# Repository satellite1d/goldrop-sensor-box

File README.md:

# goldrop-sensor-box
Temperature and humidity sensor through wifi with 230VAC power input.

The device runs on ESP32-C3-WROOM chip utilizing the built in wifi antenna, and can be powered with usb-c or up to 230V mains.
Main purpose of the device is to collect temperature and humidity data and sending it to a server through wifi in real time.
Firmware has been vibe coded.

## Firmware
Current firmware 0.6.1 for ESP32-C3 using ESP-IDF 6.1 and PlatformIO.
more info in [`goldrop-fw/`](goldrop-fw/) 

## Schematic

Pliki schematu, PCB i bibliotek: [KiCad/](KiCad/).

## PCB design
TODO: 
  - add a picture with all components
  - varistor might not be necessary
  - maybe change the LDO to a bigger one for better longevity 

## Case design
TODO: add case photo and files

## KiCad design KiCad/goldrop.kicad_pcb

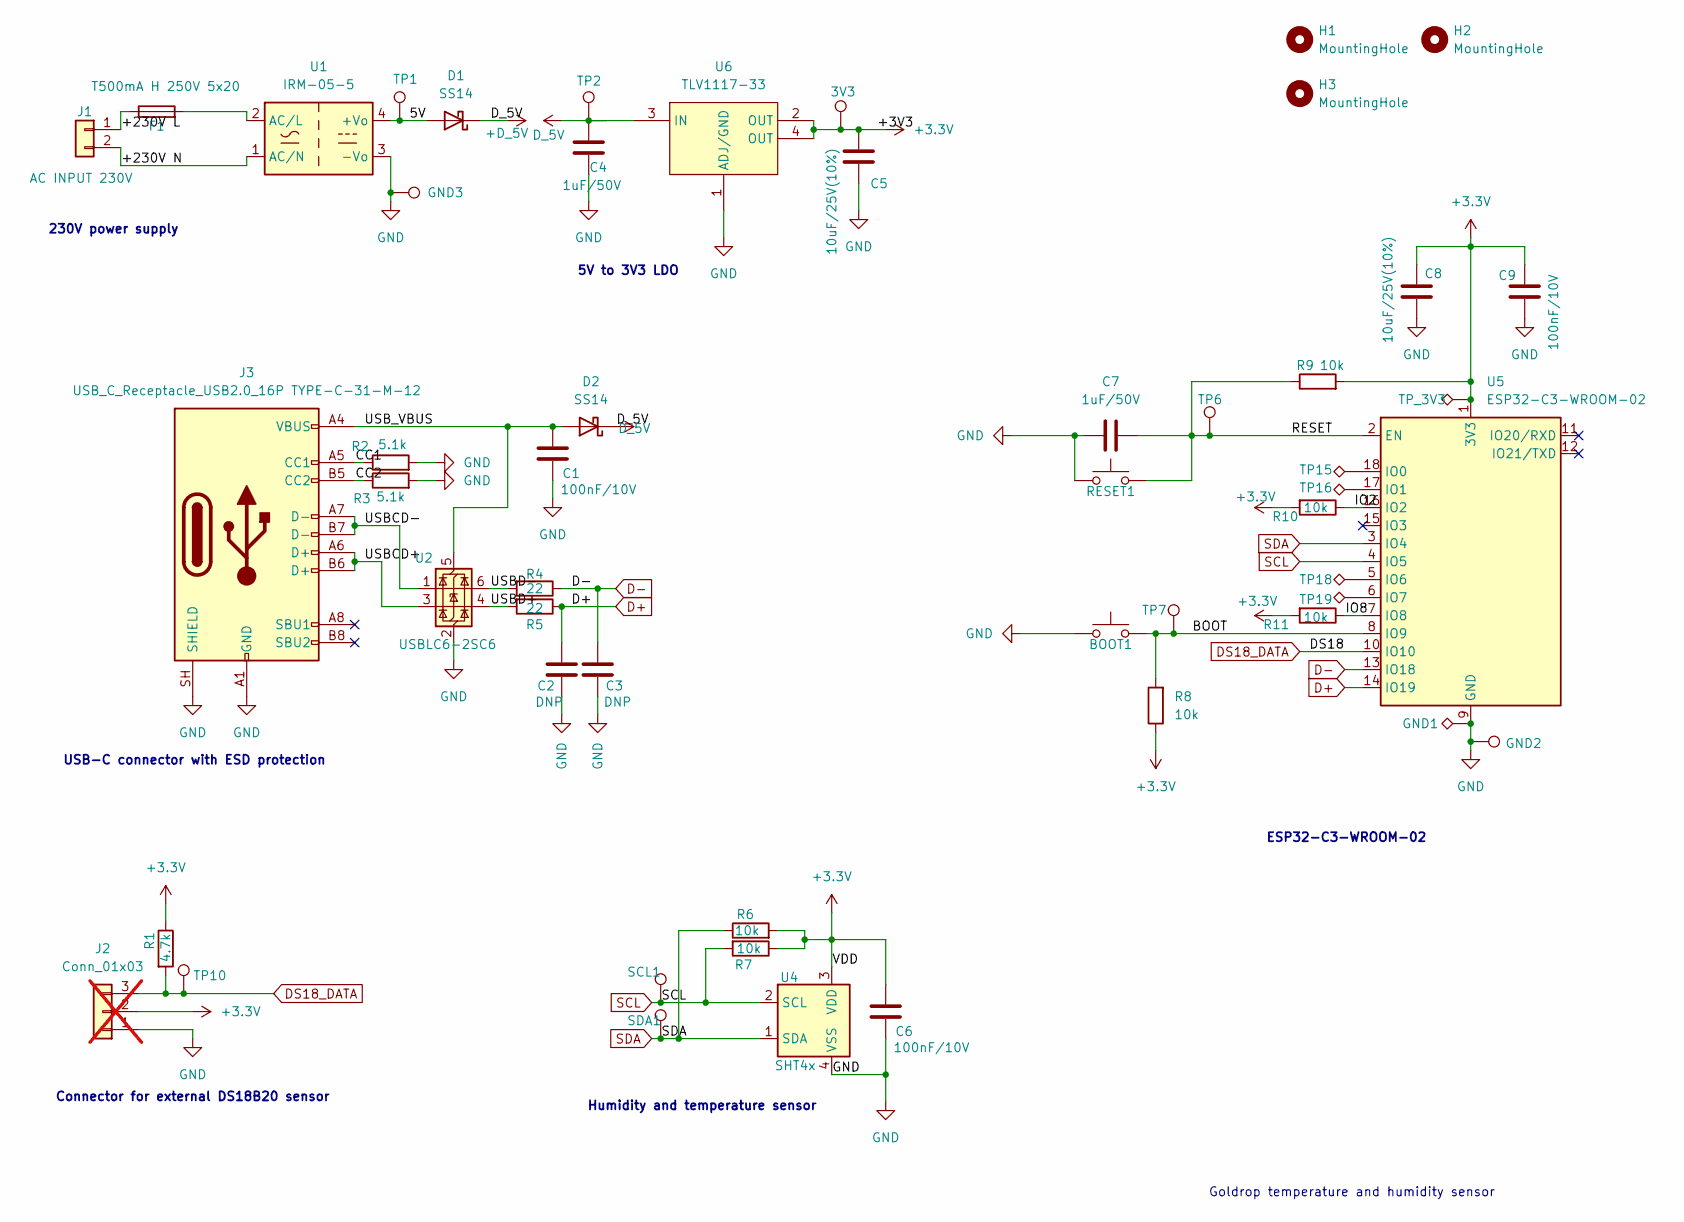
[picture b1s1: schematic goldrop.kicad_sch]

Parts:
3V3: TestPoint; TestPoint_Pad_D1.5mm
BOOT1: SW_Push; SW-SMD_L3.9-W3.0-P4.45; MPN TS-1088-AR02016; LCSC C720477
C1, C6, C9: 100nF/10V; C_0805_2012Metric_Pad1.18x1.45mm_HandSolder; MPN CC0805KRX7R9BB104; LCSC C49678
C2, C3: DNP; C_0805_2012Metric_Pad1.18x1.45mm_HandSolder
C4, C7: 1uF/50V; C_0805_2012Metric_Pad1.18x1.45mm_HandSolder; MPN CL21B105KBFNNNE; LCSC C28323
C5, C8: 10uF/25V(10%); C_0805_2012Metric_Pad1.18x1.45mm_HandSolder; MPN CL21A106KAYNNNE; LCSC C15850
D1, D2: SS14; D_SMA; MPN SS14; LCSC C2480
F1: T500mA H 250V 5x20; FUSE-TH_L22.6-W9.0; MPN 5x20 BLX-A XC-7; LCSC C3131
GND1: TestPoint_Alt; TestPoint_Pad_1.0x1.0mm
GND2, GND3: TestPoint; TestPoint_Pad_D1.5mm
H1, H2, H3: MountingHole; MountingHole_3.2mm_M3
J1: AC INPUT 230V; CONN-TH_2P-P7.62_DB910-7.62-2P; MPN DB910-7.62-2P-GN-S; LCSC C395876
J2: Conn_01x03; CONN-TH_3P-P5.08_KF129-5.08-3P; MPN KF129-5.08-3P; LCSC C475093; not fitted
J3: USB_C_Receptacle_USB2.0_16P TYPE-C-31-M-12; USB_C_Receptacle_HRO_TYPE-C-31-M-12; MPN TYPE-C-31-M-12; LCSC C165948
R1: 4.7k; R_0805_2012Metric_Pad1.20x1.40mm_HandSolder; MPN 0805W8F4701T5E; LCSC C17673
R2, R3: 5.1k; R_0805_2012Metric_Pad1.20x1.40mm_HandSolder; MPN 0805W8F5101T5E; LCSC C27834
R4, R5: 22; R_0805_2012Metric_Pad1.20x1.40mm_HandSolder; MPN 0805W8F220JT5E; LCSC C17561
R6, R7, R8, R9, R10, R11: 10k; R_0805_2012Metric_Pad1.20x1.40mm_HandSolder; MPN 0805W8F1002T5E; LCSC C17414
RESET1: SW_Push; SW-SMD_L3.9-W3.0-P4.45; MPN TS-1088-AR02016; LCSC C720477
SCL1: TestPoint; TestPoint_Pad_D1.5mm
SDA1: TestPoint; TestPoint_Pad_D1.5mm
TP1, TP2, TP6, TP7, TP10: TestPoint; TestPoint_Pad_D1.5mm
TP15, TP16, TP18, TP19: TestPoint_Alt; TestPoint_Pad_1.0x1.0mm
TP_3V3: TestPoint_Alt; TestPoint_Pad_1.0x1.0mm
U1: IRM-05-5; Converter_ACDC_MeanWell_IRM-05-xx_THT; MPN IRM-05-5; LCSC C48603696
U2: USBLC6-2SC6; SOT-23-6; MPN USBLC6-2SC6; LCSC C7519
U4: SHT4x; Sensirion_DFN-4_1.5x1.5mm_P0.8mm_SHT4x_NoCentralPad; MPN SHT45-AD1F-R2; LCSC C5360602
U5: ESP32-C3-WROOM-02; MPN ESP32-C3-WROOM-02-N4; LCSC C2934560
U6: TLV1117-33; SOT-223_L6.7-W3.5-P2.30-BR; MPN TLV1117LV33DCYR; LCSC C15578

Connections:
+3.3V: 3V3.1 (1_1), C5.2, C6.2, C8.2, C9.2, J2.2, R1.1, R6.2, R7.1, R8.1, R9.2, R10.2, R11.2, TP_3V3.1 (1_1), U4.3 (VDD), U5.1 (3V3), U6.2 (OUT), U6.4 (OUT)
+D_5V: C4.2, D1.1 (K), D2.1 (K), TP2.1 (1_1), U6.3 (IN)
/5V: D1.2 (A), TP1.1 (1_1), U1.4 (+Vo)
/+230V L: F1.1, J1.1
/+230V N: J1.2, U1.1 (AC/N)
/BOOT: BOOT1.2, R8.2, TP7.1 (1_1), U5.8 (IO9)
/CC1: J3.A5 (CC1), R2.1
/CC2: J3.B5 (CC2), R3.1
/IO2: R10.1, U5.16 (IO2)
/IO8: R11.1, U5.7 (IO8)
/RESET: C7.2, R9.1, RESET1.2, TP6.1 (1_1), U5.2 (EN)
/USBCD+: J3.A6 (D+), J3.B6 (D+), U2.3 (I/O2)
/USBCD-: J3.A7 (D-), J3.B7 (D-), U2.1 (I/O1)
/USBD+: R5.2, U2.4 (I/O2)
/USBD-: R4.2, U2.6 (I/O1)
/USB_VBUS: C1.2, D2.2 (A), J3.A4 (VBUS), J3.A9 (VBUS), J3.B4 (VBUS), J3.B9 (VBUS), U2.5 (VBUS)
D+: C2.2, R5.1, U5.14 (IO19)
D-: C3.2, R4.1, U5.13 (IO18)
DS18_DATA: J2.3, R1.2, TP10.1 (1_1), U5.10 (IO10)
GND: BOOT1.1, C1.1, C2.1, C3.1, C4.1, C5.1, C6.1, C7.1, C8.1, C9.1, GND1.1 (1_1), GND2.1 (1_1), GND3.1 (1_1), J2.1, J3.A1 (GND), J3.A12 (GND), J3.B1 (GND), J3.B12 (GND), J3.SH (SHIELD), R2.2, R3.2, RESET1.1, U1.3 (-Vo), U2.2 (GND), U4.4 (VSS), U5.9 (GND), U5.19 (GND), U6.1 (ADJ/GND)
unnamed: F1.2, U1.2 (AC/L)
unnamed: TP15.1 (1_1), U5.18 (IO0)
unnamed: TP16.1 (1_1), U5.17 (IO1)
unnamed: TP18.1 (1_1), U5.5 (IO6)
unnamed: TP19.1 (1_1), U5.6 (IO7)
SCL: R7.2, SCL1.1 (1_1), U4.2 (SCL), U5.4 (IO5)
SDA: R6.1, SDA1.1 (1_1), U4.1 (SDA), U5.3 (IO4)

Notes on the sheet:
Connector for external DS18B20 sensor
Humidity and temperature sensor
USB-C connector with ESD protection
230V power supply
Goldrop temperature and humidity sensor
ESP32-C3-WROOM-02
5V to 3V3 LDO

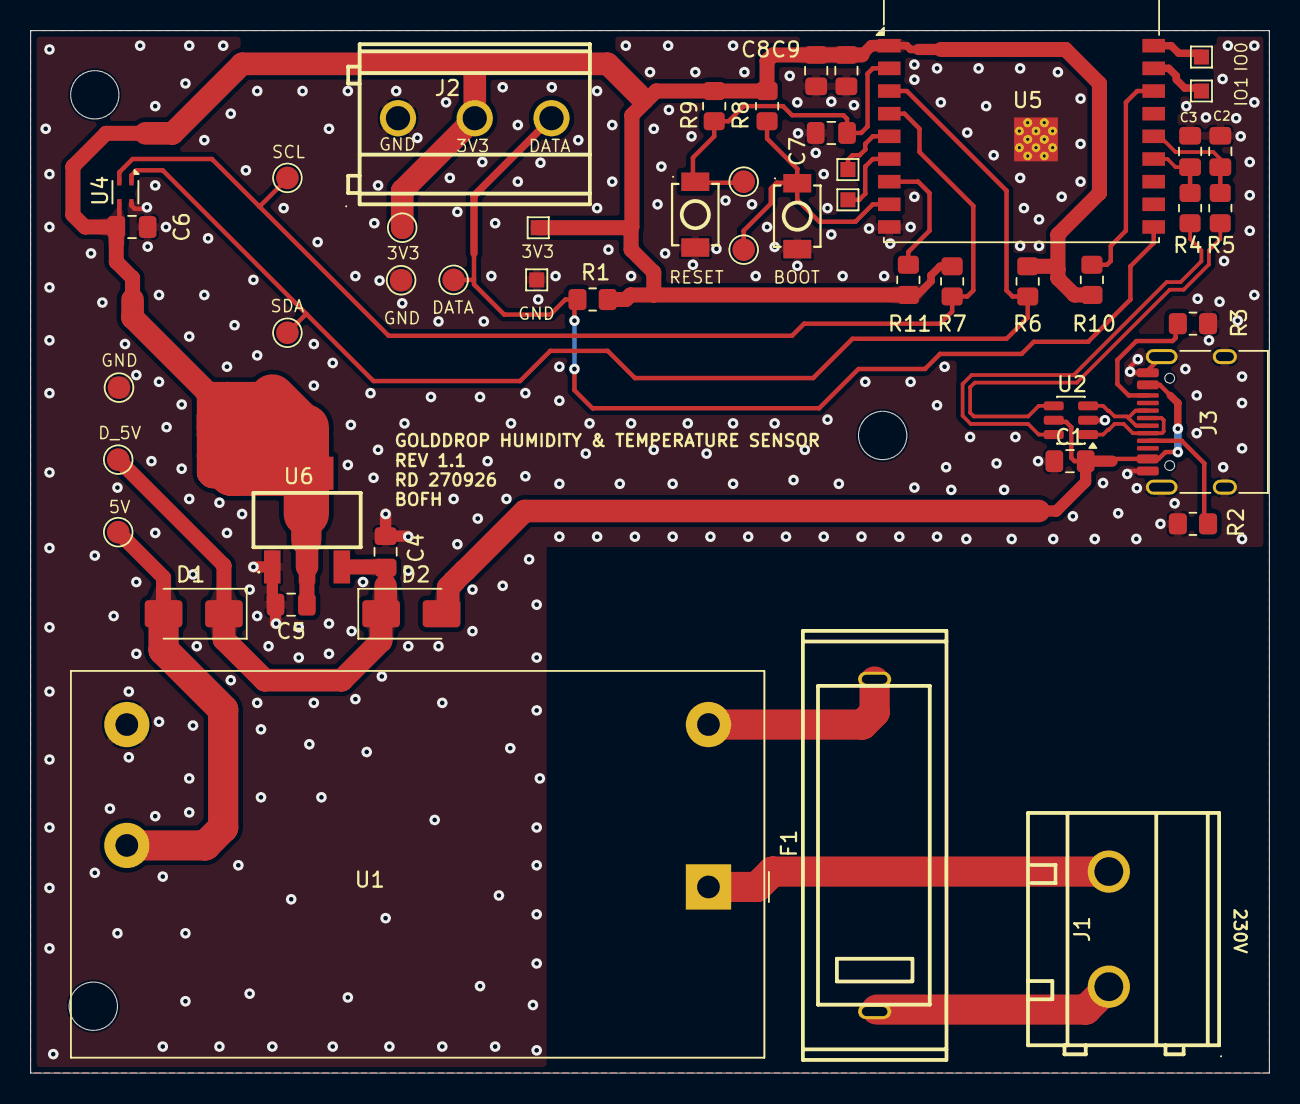
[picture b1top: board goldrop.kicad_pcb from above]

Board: 2 copper layers, 82.0 x 69.0 mm, 52 parts (0 on the bottom side), 27 nets.
